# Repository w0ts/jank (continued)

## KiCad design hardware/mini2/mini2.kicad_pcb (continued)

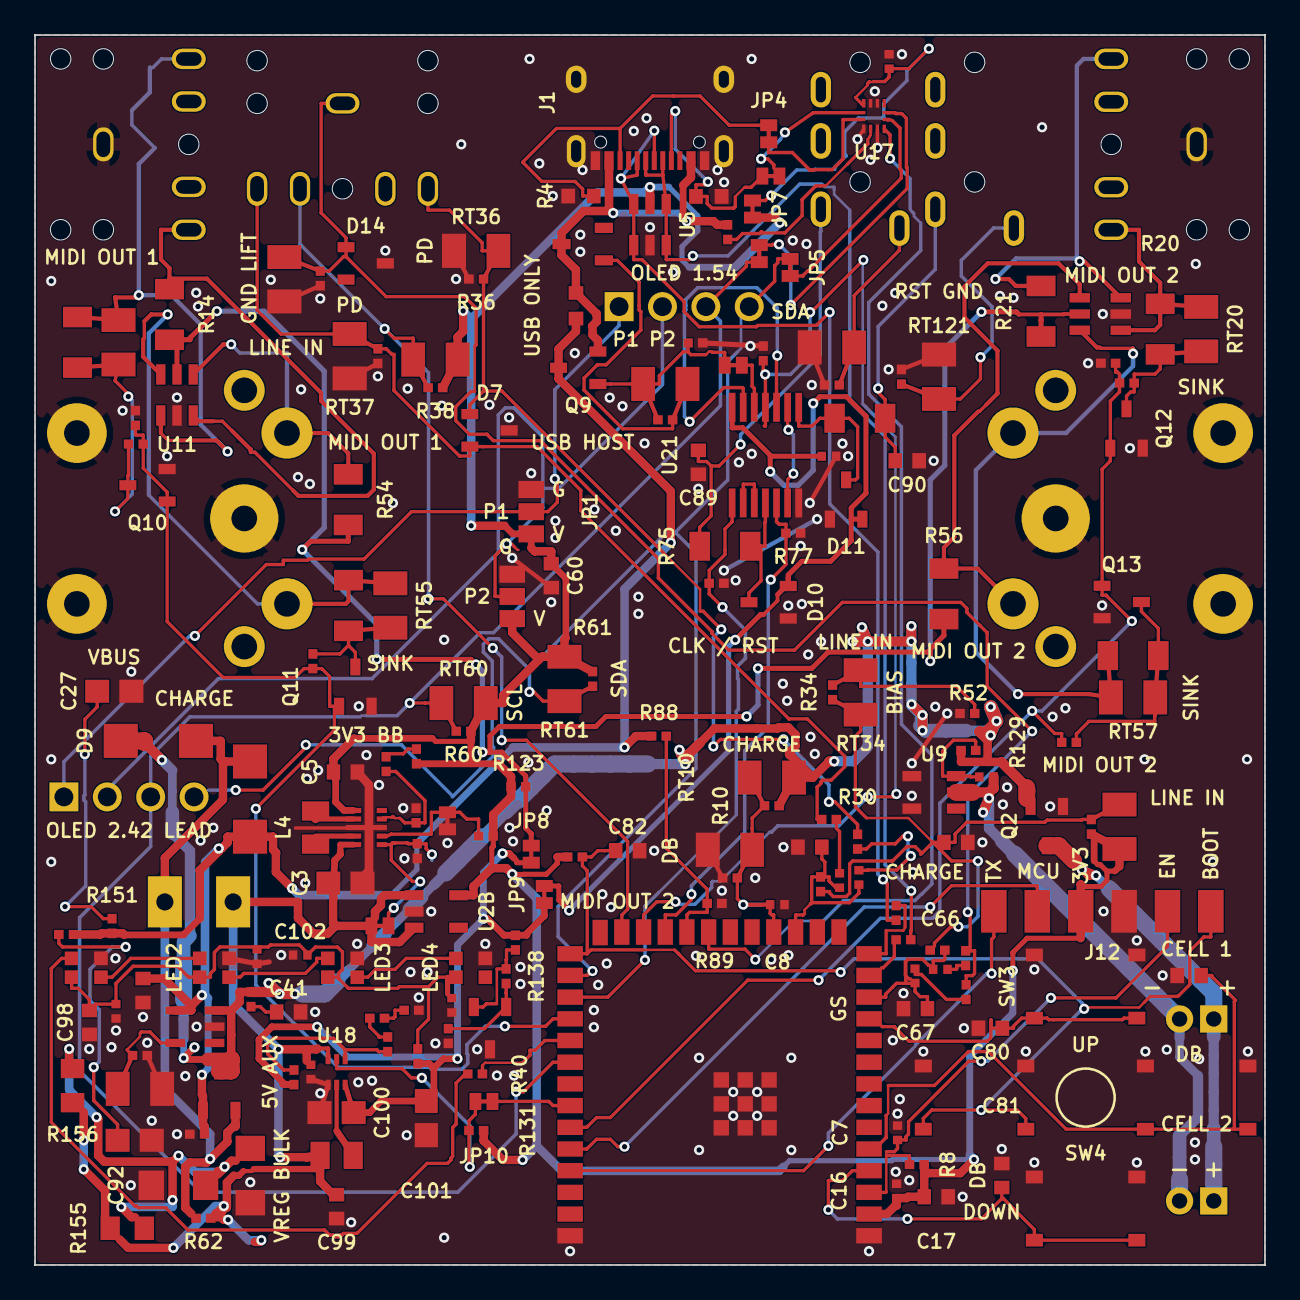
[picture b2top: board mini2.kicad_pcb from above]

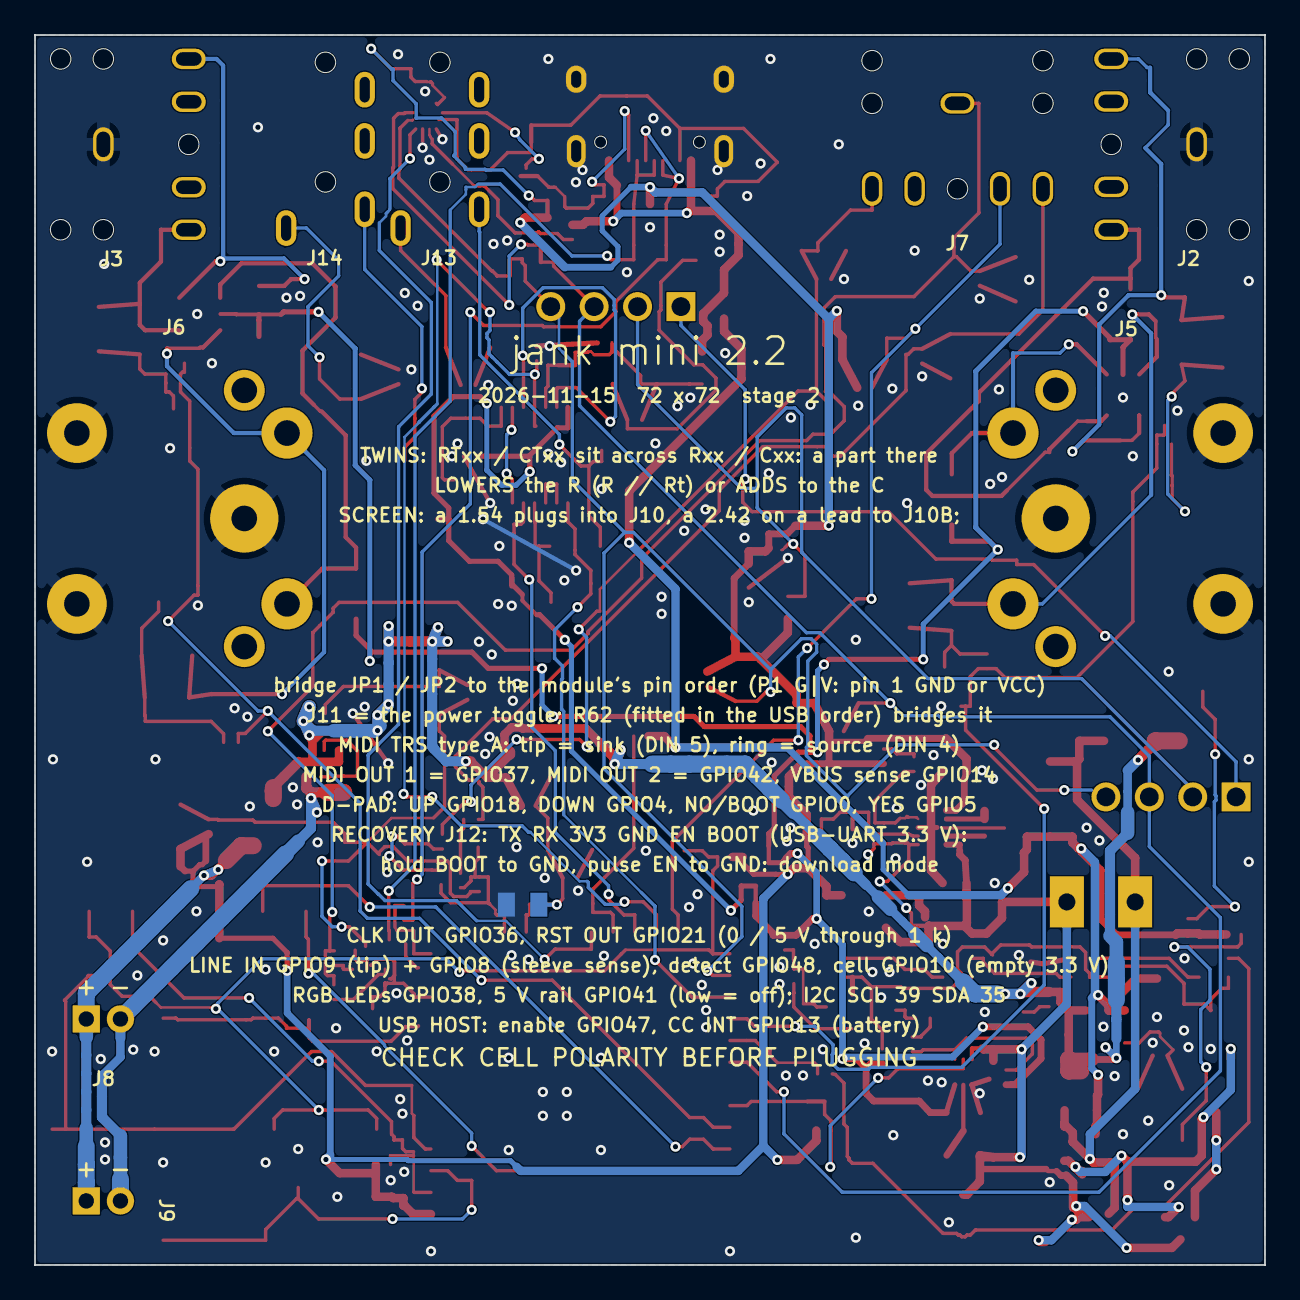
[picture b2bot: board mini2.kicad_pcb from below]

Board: 2 copper layers, 72.0 x 72.0 mm, 195 parts (10 on the bottom side), 105 nets.

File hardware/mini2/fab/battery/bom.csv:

"Comment","Designator","Footprint","LCSC Part #"
"22u","C3","C0805","C45783"
"22u","C5,C17","C0603","C59461"
"1u","C7,C30,C31,C65,C66","C0402","C52923"
"100n","C8,C16,C42,C95,C96,C97,C102,C103,C105","C0402","C1525"
"10u 25V","C27,C91,C100,C101","C0805","C15850"
"2.2n C0G","C32,C67,C89,C90","C0603","C2991172"
"10u","C33,C40,C41,C60,C98,C99","C0603","C19702"
"100u","C72,C92","C1206","C15008"
"10u","C104","C0402","C15525"
"SS34","D3,D9","SMA_L4.3-W2.6-LS5.2-RD","C8678"
"PESD15VL2BT","D7,D14","SOT-23_L2.9-W1.3-P1.90-LS2.4-BR","C38838"
"BAV99","D10,D11","SOT-23_L2.9-W1.3-P1.90-LS2.4-BR","C2500"
"BAT54C","D16","SOT-23-3_L2.9-W1.6-P1.90-LS2.8-BR","C37704"
"USB-C 16P","J1","USB-C-SMD_TYPE-C-16PIN-2MD-073","C2765186"
"0.47u","L4,L5","IND-SMD_L2.0-W1.6-1","C668312"
"WS2812C-2020-V6","LED1,LED2,LED3,LED4","LED-SMD_4P-L2.2-W2.0-P1.00_WS2815C-2020-4P","C55109522"
"AO3401A","Q1,Q2,Q9","SOT-23_L2.9-W1.3-P1.90-LS2.4-BR","C15127"
"AO3400A","Q10,Q11,Q12,Q13","SOT-23_L2.9-W1.3-P1.90-LS2.4-BR","C20917"
"10k","R8,R16","R0402","C25744"
"1M","R10,R11,R38,R134","R0402","C26083"
"220","R14,R15,R20,R21,R54,R55,R56,R57","R1206","C17957"
"22","R24,R25,R40","R0402","C25092"
"20k","R30,R31,R65,R66,R92,R138,R139,R142,R153,R154","R0402","C25765"
"12k","R32,R51,R67,R146","R0402","C25752"
"150k","R33,R89","R0402","C25755"
"100k","R34,R36,R37,R50,R71,R77,R88,R91,R124,R125,R131,R135,R140,R141","R0402","C25741"
"100","R39,R52,R120,R121","R0402","C25076"
"2.2k","R60,R61,R93","R0402","C25879"
"1k","R75,R81","R1206","C4410"
"1","R86,R151,R152","R0402","C25086"
"910k","R94","R0402","C25800"
"10","R98,R145","R0402","C25077"
"22k","R136","R0402","C25768"
"1","R155,R156","R0805","C25271"
"DOWN / UP / YES / NO / BOOT","SW1,SW3,SW4,SW5","SW-SMD_4P-L5.1-W5.1-P3.70-LS6.5-TL_H1.5","C318884"
"ESP32-S3-WROOM-1U-N8R2","U1","WIRELM-SMD_ESP32-S3-WROOM-1U","C3013944"
"TPS63802DLAR","U2","VSON-10_L3.0-W2.0-P0.50-TL","C2845237"
"SRV05-4","U5,U11,U12","SOT-23-6_L2.9-W1.6-P0.95-LS2.8-BL-1","C7420376"
"TP4054-42","U8","SOT-23-5_L3.0-W1.7-P0.95-LS2.8-BL","C32574"
"XB5353A","U9","SOT-23-5_L3.0-W1.7-P0.95-LS2.8-BR","C80628"
"TUSB320LIRWBR","U17","X2QFN-12_L1.6-W1.6-P0.40-TL","C2836598"
"TPS61023DRLR","U18","SOT-563_L1.6-W1.2-P0.50-LS1.6-BR","C919459"
"CJ431","U19","SOT-23-3_L2.9-W1.6-P1.90-LS2.8-BR","C3113"
"74AHCT04","U21","TSSOP-14_L5.0-W4.4-P0.65-LS6.4-BL","C8190"

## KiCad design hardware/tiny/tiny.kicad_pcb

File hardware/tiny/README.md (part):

# Jank tiny: a small board anyone orders assembled from JLCPCB

Part of the **[Jank device](../../README.md)** · the study behind it: [docs/dongle.md](../../docs/dongle.md) · the
bigger board: [hardware/pcb](../pcb/README.md)

One board, two uses. **With a computer on USB-C it is the Jank stick** (network adapter, USB-MIDI, the drive).
**Alone, plugged into a piece of gear's MIDI OUT or THRU, it runs from that output's few milliamps** and sends jank's
MIDI clock into the gear's MIDI IN. An ESP32-S3-MINI-1-N8 module, a USB-C on the top edge, a 3.5 mm TRS jack on each side
(left: MIDI OUT, right: POWER IN, both via TRS-to-DIN type A adaptors), one button, one LED, a 4.4 mF reservoir and a
60 nA buck. Everything is generated by the scripts here, from one parts table (`parts.py`).

> **Stage: design for review (2026-11-10).** Nothing is ordered, built or measured. Every figure marked *unverified*
> comes from a drawing, a datasheet or an estimate, not from a part in hand. Prices and stock are one snapshot
> (`fab/parts-snapshot.json`, read 2026-11-10 from JLCPCB's parts search), not a quote.

**Two variants, from the same schematic and scripts** (the user's ruling 2026-11-10: halve the area; cost both):

| | **tiny** (the board) | tiny-1s (for comparison) |
|---|---|---|
| Size | **27.0 x 36.0 mm** (972 mm²) | 42.0 x 44.0 mm (1848 mm²) |
| Sides | **two**: the cans, the jacks and small parts on the bottom (JLC *Standard* assembly) | one (JLC *Economic* assembly) |
| Board, assembly files | `tiny.kicad_pcb`, `fab/` | `tiny-1s.kicad_pcb`, `fab/1s/` |
| Renders, mockup | `render-top.png`, `render-bottom.png`, `mockup.stl` | `render-top-1s.png`, `render-bottom-1s.png`, `mockup-1s.stl` |
| Case | `case/` (made for this one) | none |

The cost of each, at 5 and 30 boards: **"Cost"** below (`fab/cost.md`).

## Files

| File | What |
|---|---|
| `parts.py` | **The parts table**: every part, its value, JLC footprint, LCSC code and the net on each pad; the GPIO map |
| `fetch_jlc.sh` | Fetches JLC's own footprints (EasyEDA, via easyeda2kicad 1.0.1) into `lib/jlc.pretty` (committed; run only to refresh) |
| `make_footprints.py` | `lib/tiny.pretty`: the JLC footprints with their silkscreen dropped, peg holes made unplated and courtyards redrawn; the cable pads |
| `make_schematic.py` | `tiny.kicad_sch` (every pin labelled, no wires), `tiny.kicad_pro`, `lib/tiny.kicad_sym`, `fab/intended-nets.json` |
| `route.py` | A small two-layer grid router (A*, vias, clearance masks per track width): no autorouter is installed here |
| `make_board.py` | `tiny.kicad_pcb` / `tiny-1s.kicad_pcb` (`VARIANT=2s|1s`): placement, routing (with rip-up and retry), ground pours, the antenna keep-out, stitching |
| `check_nets.py` | The schematic's netlist against `parts.py`, every board pad against it, the pin rules (no strapping pin, ADC1, RTC GPIOs) |
| `make_assembly.py` | `bom.csv`, `cpl.csv` for JLCPCB; checks every part's pads against JLC's own footprint at the CPL place |
| `jlc_parts.py` | `fab/parts-snapshot.json`: stock, price breaks, Basic / Extended, from JLCPCB's public parts search |
| `cost.py` | `fab/cost.md`: the estimate per variant at 5 and 30 boards |
| `make_mockup.py` | `mockup.stl`: the board and every part as a block, one closed solid (`../check_stl.py`) |
| `make_fab.sh` | **All of it in order**, both variants, then the cost and the case |
| `case/` | `tiny_case.scad`, `make_stl.sh`, `stl/` (base, lid, button cap), `assembly.png` |
| `tiny.kicad_dru` | The one DRC exception (below) |

```
sh hardware/tiny/make_fab.sh        # KiCad 10 (kicad-cli + its Python), python3, OpenSCAD; ~15 min (the router)
ROUTE=0 sh hardware/tiny/make_fab.sh   # keep the routed boards, redo the checks and outputs
```

**For JLCPCB:** `fab/tiny-gerbers.zip` (2 layers, 1.6 mm), `fab/bom.csv`, `fab/cpl.csv`.

## Schematic

```
 J3 POWER IN (gear's MIDI OUT/THRU)            USB-C J1
   ring (DIN 4) -- R1 47R -- D1 B5819W --+       VBUS -- D3 B5819W -- R5 4.7R --+
   tip  (DIN 5) -- R2 47R -- D2 B5819W --+-- VSYS (C1 + C2: 2 x 2200 uF, C3 10 uF)
   sleeve (DIN 2) = GND                    |      CC1, CC2: 5.1k to GND (R3, R4); D+/D- to GPIO20/19
                                           +-- U2 TPS62842 VIN; R7 51k = 3.3 V; L1 2.2 uH; C5 22 uF -> +3V3
                                           +-- U3 BL8506-40 (4.0 V detector) -- D4 A1 --+
                         PWR_HOLD (GPIO4) ---------------------------- D4 A2 --+-- BUCK_EN (C4 100n, R6 10M to GND)
                         VBUS ---------------------------------------- D5 --- +
                                           +-- R10 1M -- VBANK_ADC (GPIO1, C8 100n) -- R11 1M -- GND
 J2 MIDI OUT (gear's MIDI IN)                 VBUS -- R12 100k -- VBUS_SENSE (GPIO2) -- R13 100k -- GND
   ring (DIN 4) -- R14 33R -- +3V3
   tip  (DIN 5) -- R15 10R -- MIDI_TX (GPIO21)
   sleeve (DIN 2) = GND                        +3V3 -- R8 10k -- EN, C7 1u;  GPIO0 -- SW1 -- GND;  GPIO38 -- R9 5.1k -- LED1 -- GND
```

### Power from a MIDI OUT

- **Both data pins feed the reservoir:** the ring (DIN pin 4, the sender's source through its 220 ohm) and the tip (DIN
  pin 5, high between bytes), each through **47 ohm** and a **B5819W** Schottky. Nothing flows back out: each diode
  blocks when its pin is below VSYS (the tip during a 0 bit, any pin when USB holds VSYS up), leaving only the diode's
  leakage (microamps, *unverified* at these voltages).
- **The 47 ohm current limit, the trade-off:** it lowers the current from a normal 5 V / 220 ohm output only a little
  at the operating point (bank at 4.0 V, Schottky 0.25 V: (5 - 0.25 - 4.0) / 267 = **2.8 mA a pin instead of 3.4 mA**,
  -18 %; the running equilibrium with ~2.3 mA drawn moves from ~4.50 V to ~4.46 V), but it guards weak drivers when the
  bank is empty: into a flat bank a 5 V / 220 ohm output gives 17.6 mA instead of 21 mA, a **3.3 V / 33 ohm output
  (CA-033) 38 mA instead of 92 mA**. Such 3.3 V gear cannot run the dongle anyway (the bank never reaches the start
  threshold), but it is not stressed either. 47 ohm is a JLC Basic part.
- **USB joins the same rail** through D3 (B5819W) and **R5 4.7 ohm**: USB wins when present (4.7 V against the bank's
  ~4.4 V). R5 limits the inrush into 4.4 mF to ~1 A (time constant ~21 ms) instead of an unlimited surge; in stick
  mode it drops ~0.47 V at 100 mA (47 mW). *Unverified:* the 0805's pulse rating for ~49 mJ per plug-in, and that every
  host tolerates the 1 A peak (USB 2.0 allows 10 uF at attach). A 1206 (Extended) is the safer choice if it is a
  concern.

### The reservoir (C1, C2: 2 x 2200 uF 6.3 V aluminium, 10 x 10.5 mm, **4.4 mF**)

- **The start:** the module may only start once the bank holds a whole boot: the detector releases the buck at
  **~4.16 V** (BL8506-40: 4.00 V falling, 0.16 V hysteresis typical, 4.0..4.32 V rising), and the module runs down to
  ~3.2 V at the bank (the buck in 100 % mode; the S3 needs 3.0 V). **~1.0 V x 4.4 mF = 4.4 mC: about 150 ms of boot at
  30 mA** (the boot's current and length are *unmeasured*: the study's "a few mF for a slow start").
- **The listening windows:** 0.6..0.8 mC each (the study's estimate) sag the bank only **0.15..0.18 V**.
- **Charging from a 5 V output:** both pins together give ~5..7 mA into an empty bank: **~3 s** to the start threshold.
- **Why these parts:** no supercap is placeable at JLC; MLCCs lose most of their capacitance at 4 V bias (dozens
  needed); tantalum is ~10x the price. Two 10 x 10 mm cans store the most per board area of the SMD aluminium parts
  JLC stocks (1000 uF 8 x 10: 88 mm²/mF of footprint; 2200 uF 10 x 10: 65 mm²/mF).
- **Leakage** (*unverified*, the one figure that matters most here): the datasheet's limit, 0.01 CV, is ~139 uA a can
  at rated voltage after 2 minutes; aluminium caps at 70 % of rating after hours typically leak a few percent of that.
  **Measure it**: it adds directly to the 3 mA budget.
- 6.3 V rating: the rail never exceeds VBUS (5.25 V, 5.5 V from a careless charger) minus a Schottky.

### 3.3 V: the TPS62842 buck (chosen) against an LDO

| | TPS62842DGRR (C2873354) + 2.2 uH | RT9080-33 LDO (C841192) | XC6206P332 LDO (C5446, Basic) |
|---|---|---|---|
| Quiescent current | **60 nA** (120 nA in 100 % mode) | 2 uA | 1 uA |
| Input current for 2.5 mA out at 4.4 V (85 % efficient, *the efficiency at this load unverified*) | **~2.2 mA** | 2.5 mA | 2.5 mA |
| Peak current (Wi-Fi TX in stick mode, ~350 mA) | 750 mA | 600 mA | **200 mA: too weak** |
| Price (snapshot) | $0.40 + $0.11 inductor, 2 Extended lines | $0.12, 1 Extended line | $0.13 Basic |

The buck saves ~0.3 mA of the ~2.5 mA the study budgets (12 %; more as the bank rises) for ~$0.40 a board and one
more Extended line: on a 5 mA source that is the margin. R7 = **51 k** sets 3.3 V (TI table 1: 50.21..54.39 k; 51 k is
a Basic part, 52.3 k is not). MODE low: power-save (PFM) mode.

### Start-up and holding the buck on (BUCK_EN)

BUCK_EN = the detector **or** VBUS **or** PWR_HOLD (GPIO4), through D4 / D5 (BAV70, nanoamp leakage). C4 (100 nF) and
R6 (10 M) keep it high **~1 s after** the detector drops (the buck's EN pull-down is off once it runs, TI datasheet
8.3): time for the firmware to raise PWR_HOLD. **The firmware must set PWR_HOLD high early (a bootloader hook if the
boot is slow) and keep it held in light and deep sleep** (an RTC GPIO: `rtc_gpio_hold_en`); releasing it below 4.0 V
switches everything off until the bank is back above ~4.16 V. A brown-out during the boot cannot loop: the timer ends,
the bank recharges, it starts again. With USB, VBUS holds BUCK_EN.

### Static draw, everything off (the bank charging, *datasheet typicals*)

Detector 0.5 uA, the VSYS divider 2.4 uA at 4.8 V, the buck's shutdown 25 nA, R6 0.4 uA while BUCK_EN is high, the
diodes' leakage: **~3 uA plus the cans' leakage**.

## Pin map (for the firmware's board.h)

| Function | GPIO | Module pin | Notes |
|---|---|---|---|
| **MIDI_TX** | **21** | 25 | UART TX (any UART by the GPIO matrix), idle high; through R15 10 ohm to the MIDI OUT tip. An RTC GPIO: the ULP can send the ticks. Not strapping |
| **LED** | **38** | 34 | active high, R9 5.1 k: ~0.27 mA lit (red, 1.9 V) |
| **BOOT / user button** | **0** | 4 | to GND; held at reset = download mode. Internal pull-up |
| **VBANK_ADC** | **1** | 5 | ADC1_CH0: VSYS / 2 (1 M / 1 M, 100 nF); 11 dB attenuation reads to ~3.1 V = 6.2 V at the bank |
| **VBUS_SENSE** | **2** | 6 | ADC1_CH1 or digital: VBUS / 2 (100 k / 100 k) = 2.5 V when USB is plugged |
| **PWR_HOLD** | **4** | 8 | high keeps the buck on; hold it through sleep (RTC GPIO) |
| USB D- / D+ | 19 / 20 | 23 / 24 | the native USB (stick mode) |
| EN | | 45 | RC reset (R8 10 k, C7 1 uF); no reset button |
| MIDI OUT ring | | | +3V3 through R14 33 ohm (0805) |

Not used, left open: everything else, including the strapping pins GPIO3, 45, 46 and the console UART (GPIO43 / 44).

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
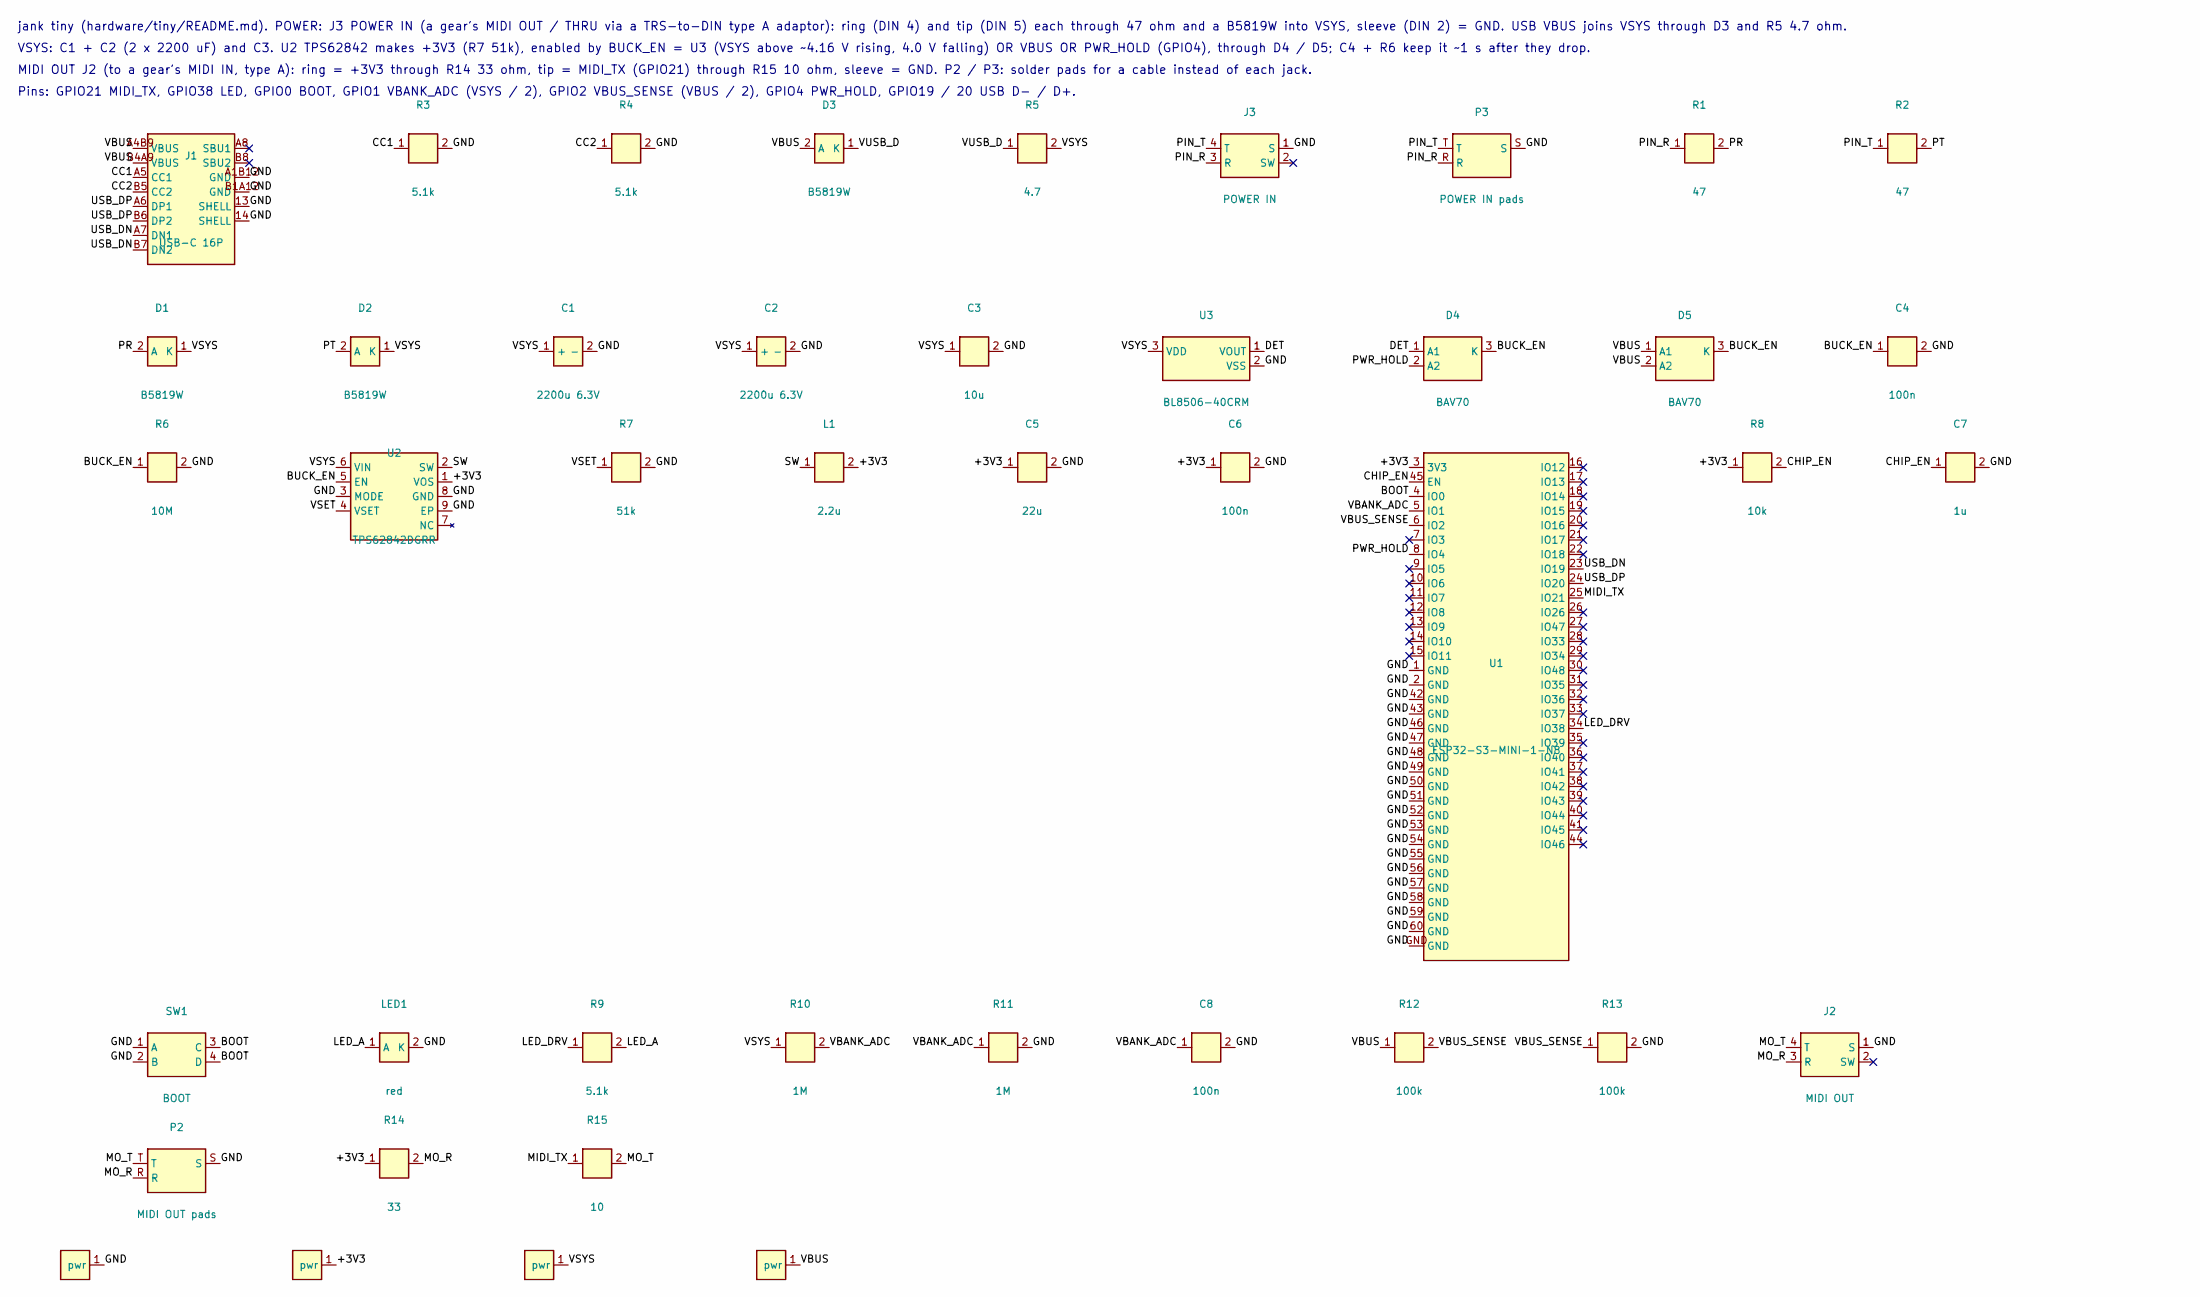
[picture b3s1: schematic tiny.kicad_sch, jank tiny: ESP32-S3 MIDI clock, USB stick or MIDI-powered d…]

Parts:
C1, C2: 2200u 6.3V; CAP-SMD_BD10.0-L10.3-W10.3-LS11.0-FD; LCSC C22383517
C3: 10u; C0805; LCSC C15850
C4, C6, C8: 100n; C0603; LCSC C14663
C5: 22u; C0805; LCSC C45783
C7: 1u; C0603; LCSC C15849
D1, D2, D3: B5819W; SOD-123_L2.7-W1.6-LS3.7-RD-1; LCSC C8598
D4, D5: BAV70; SOT-23-3_L3.0-W1.7-P0.95-LS2.9-BR; LCSC C68978
J1: USB-C 16P; USB-C-SMD_TYPE-C-16PIN-2MD-073; LCSC C2765186
J2: MIDI OUT; AUDIO-SMD_XKB_PJ-320D-B; LCSC C2884940
J3: POWER IN; AUDIO-SMD_XKB_PJ-320D-B; LCSC C2884940
L1: 2.2u; L0806; LCSC C79317
LED1: red; LED-SMD_L1.6-W0.8-R-RD; LCSC C2286
P2: MIDI OUT pads; TRS_PADS_3x1.0mm
P3: POWER IN pads; TRS_PADS_3x1.0mm
R1, R2: 47; R0603; LCSC C23182
R3, R4, R9: 5.1k; R0603; LCSC C23186
R5: 4.7; R0805; LCSC C17675
R6: 10M; R0603; LCSC C7250
R7: 51k; R0603; LCSC C23196
R8: 10k; R0603; LCSC C25804
R10, R11: 1M; R0603; LCSC C22935
R12, R13: 100k; R0603; LCSC C25803
R14: 33; R0805; LCSC C17634
R15: 10; R0603; LCSC C22859
SW1: BOOT; SW-SMD_4P-L5.1-W5.1-P3.70-LS6.5-TL_H1.5; LCSC C318884
U1: ESP32-S3-MINI-1-N8; BULETM-SMD_ESP32-S3-MINI-1-N8; LCSC C2913206
U2: TPS62842DGRR; HVSSOP-8_L3.0-W3.0-P0.65-LS4.9-BL-EP; LCSC C2873354
U3: BL8506-40CRM; SOT-23-3_L2.9-W1.6-P1.90-LS2.8-BR; LCSC C2909397

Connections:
+3V3: C5.1, C6.1, L1.2, R8.1, R14.1, U1.3 (3V3), U2.1 (VOS)
BOOT: SW1.3 (C), SW1.4 (D), U1.4 (IO0)
BUCK_EN: C4.1, D4.3 (K), D5.3 (K), R6.1, U2.5 (EN)
CC1: J1.A5 (CC1), R3.1
CC2: J1.B5 (CC2), R4.1
CHIP_EN: C7.1, R8.2, U1.45 (EN)
DET: D4.1 (A1), U3.1 (VOUT)
GND: C1.2 (-), C2.2 (-), C3.2, C4.2, C5.2, C6.2, C7.2, C8.2, J1.13 (SHELL), J1.14 (SHELL), J1.A1B12 (GND), J1.B1A12 (GND), J2.1 (S), J3.1 (S), LED1.2 (K), P2.S, P3.S, R3.2, R4.2, R6.2, R7.2, R11.2, R13.2, SW1.1 (A), SW1.2 (B), U1.1 (GND), U1.2 (GND), U1.42 (GND), U1.43 (GND), U1.46 (GND), U1.47 (GND), U1.48 (GND), U1.49 (GND), U1.50 (GND), U1.51 (GND), U1.52 (GND), U1.53 (GND), U1.54 (GND), U1.55 (GND), U1.56 (GND), U1.57 (GND), U1.58 (GND), U1.59 (GND), U1.60 (GND), U1.GND, U2.3 (MODE), U2.8 (GND), U2.9 (EP), U3.2 (VSS)
LED_A: LED1.1 (A), R9.2
LED_DRV: R9.1, U1.34 (IO38)
MIDI_TX: R15.1, U1.25 (IO21)
MO_R: J2.3 (R), P2.R, R14.2
MO_T: J2.4 (T), P2.T, R15.2
PIN_R: J3.3 (R), P3.R, R1.1
PIN_T: J3.4 (T), P3.T, R2.1
PR: D1.2 (A), R1.2
PT: D2.2 (A), R2.2
PWR_HOLD: D4.2 (A2), U1.8 (IO4)
SW: L1.1, U2.2 (SW)
USB_DN: J1.A7 (DN1), J1.B7 (DN2), U1.23 (IO19)
USB_DP: J1.A6 (DP1), J1.B6 (DP2), U1.24 (IO20)
VBANK_ADC: C8.1, R10.2, R11.1, U1.5 (IO1)
VBUS: D3.2 (A), D5.1 (A1), D5.2 (A2), J1.A4B9 (VBUS), J1.B4A9 (VBUS), R12.1
VBUS_SENSE: R12.2, R13.1, U1.6 (IO2)
VSET: R7.1, U2.4 (VSET)
VSYS: C1.1 (+), C2.1 (+), C3.1, D1.1 (K), D2.1 (K), R5.2, R10.1, U2.6 (VIN), U3.3 (VDD)
VUSB_D: D3.1 (K), R5.1

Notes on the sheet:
jank tiny (hardware/tiny/README.md). POWER: J3 POWER IN (a gear's MIDI OUT / THRU via a TRS-to-DIN type A adaptor): ring (DIN 4) and tip (DIN 5) each through 47 ohm and a B5819W into VSYS, sleeve (DIN 2) = GND. USB VBUS joins VSYS through D3 and R5 4.7 ohm.
VSYS: C1 + C2 (2 x 2200 uF) and C3. U2 TPS62842 makes +3V3 (R7 51k), enabled by BUCK_EN = U3 (VSYS above ~4.16 V rising, 4.0 V falling) OR VBUS OR PWR_HOLD (GPIO4), through D4 / D5; C4 + R6 keep it ~1 s after they drop.
MIDI OUT J2 (to a gear's MIDI IN, type A): ring = +3V3 through R14 33 ohm, tip = MIDI_TX (GPIO21) through R15 10 ohm, sleeve = GND. P2 / P3: solder pads for a cable instead of each jack.
Pins: GPIO21 MIDI_TX, GPIO38 LED, GPIO0 BOOT, GPIO1 VBANK_ADC (VSYS / 2), GPIO2 VBUS_SENSE (VBUS / 2), GPIO4 PWR_HOLD, GPIO19 / 20 USB D- / D+.

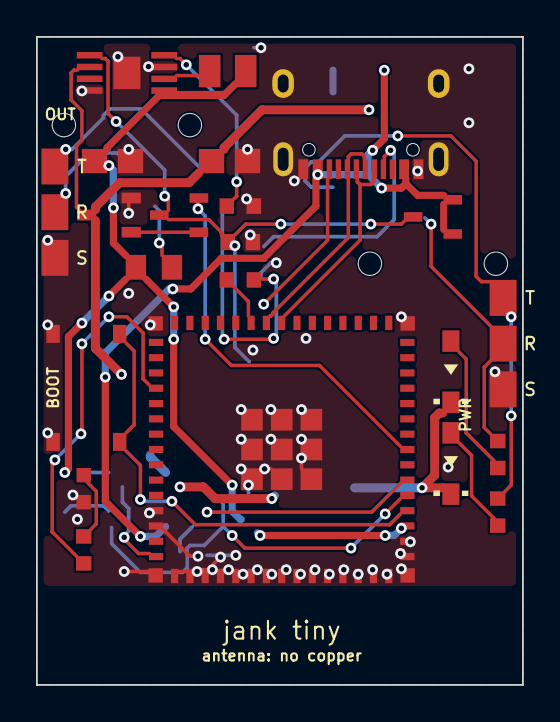
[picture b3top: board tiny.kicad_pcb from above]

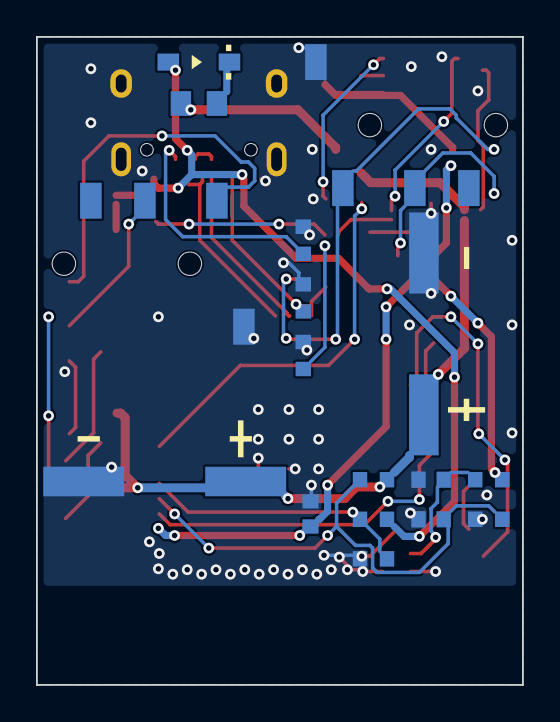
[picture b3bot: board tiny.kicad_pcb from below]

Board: 2 copper layers, 27.0 x 36.0 mm, 39 parts (17 on the bottom side), 27 nets.

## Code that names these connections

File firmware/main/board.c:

/* SPDX-License-Identifier: GPL-3.0-only */
/* The boards' pin tables and, in the auto build, which board this is (board.h). The values are the ones board.h held
 * per build until 2026-11-22; their sources stay in the comments. */
#include "board.h"
#include "esp_attr.h"
#include "esp_flash.h"
#include "esp_log.h"

static const char *TAG = "board";

#if CONFIG_JANK_BOARD_XIAO || CONFIG_JANK_BOARD_AUTO
/* Seeed XIAO ESP32S3. D6 = GPIO43 for MIDI data, the board's 3V3 pad the source; the module has 499 ohm in series on D6
 * (v1.2 schematic, R6): MIDI current about 2.3 mA (docs/boards.md). The button is BOOT, the LED the single yellow one
 * (GPIO21, active low). No CC chip, no 5 V of its own, no line in: USB host mode through an OTG adapter with self-powered
 * gear. Bench outputs (midi.c): D1 = GPIO2 changes level on every MIDI clock, D0 = GPIO1 goes high with each start
 * (docs/midi.md). The UI bench (JANK_UI_BENCH): a 128 x 64 I2C OLED on D4 = GPIO5 SDA / D5 = GPIO6 SCL, UP D3 = GPIO4,
 * DOWN D8 = GPIO7, YES D9 = GPIO8, NO D10 = GPIO9 or BOOT. The LINE IN bench (JANK_LINEIN_BENCH): pad D3 = GPIO4
 * (ADC1_CH3) through a bias network (docs/linein.md), no cell, no plug detect. */
static DRAM_ATTR const struct board XIAO = {
    .name = "xiao", .model = "XIAO",
    .button_gpio = 0, .button_active_low = 1,
    .led_rgb_gpio = -1, .led_mono_gpio = 21, .led_count = 1,
    .midi_tx_gpio = 43, .midi_source_gpio = -1, .midi_tx_more = {-1, -1}, .midi_tx_invert = 0, .midi_tx_drive = -1,
    .bench_clk_gpio = 2, .bench_rst_gpio = 1,
    .clk_gpio = -1, .rst_gpio = -1, .v5_en_gpio = -1,
#if CONFIG_JANK_UI_BENCH
    .i2c_sda_gpio = 5, .i2c_scl_gpio = 6,
    .btn_up_gpio = 4, .btn_down_gpio = 7, .btn_yes_gpio = 8, .btn_no2_gpio = 9, .oled = 1,
#else
    .i2c_sda_gpio = -1, .i2c_scl_gpio = -1,
    .btn_up_gpio = -1, .btn_down_gpio = -1, .btn_yes_gpio = -1, .btn_no2_gpio = -1, .oled = 0,
#endif
    .lcd = 0, .lcd_mosi_gpio = -1, .lcd_sclk_gpio = -1, .lcd_cs_gpio = -1, .lcd_dc_gpio = -1, .lcd_rst_gpio = -1, .lcd_bl_gpio = -1,
    .cc_scl_gpio = -1, .cc_sda_gpio = -1, .cc_int_gpio = -1,
    .host_en_gpio = -1, .vbus_sense_gpio = -1, .line_detect_gpio = -1, .pump_gpio = -1,
    .usbport_tusb320 = 0, .usbport_mini3 = 0,
    .bridge_slots_psram = 1,              /* (2026-11-22: with both boards' drivers in one image the 30 KB no longer fit in
                                             internal RAM: ui_start failed with ESP_ERR_NO_MEM, measured with `diag`) */
    .host_audio = 0,                      /* host mode: no audio client, no beat tracker: the Digitone and the Launchpad together need the RAM
                                             (the second one's claim failed with ESP_ERR_NO_MEM, 2026-11-24); the tracker did not run there anyway */
#if CONFIG_JANK_LINEIN_BENCH
    .has_linein = 1, .linein_gpio = 4,
#else
    .has_linein = 0, .linein_gpio = -1,
#endif
    .linesense_gpio = -1, .cell_gpio = -1, .cell_div = 1, .cell_empty_mv = 0,
};
#endif

#if CONFIG_JANK_BOARD_LCD2 || CONFIG_JANK_BOARD_AUTO
/* Waveshare ESP32-S3-LCD-2 (sku 30306, ESP32-S3R8, 16 MB flash) on the jank mini 3, pins from the LCD-2's schematic and
 * hardware/jank-mini-3/parts.py (docs/lcd2.md has the sources and what is not verified). The screen: 240 x 320 ST7789 on
 * SPI, landscape (lcd.c); LCD_RST is GPIO0 through R16 "NC/0R" (the panel is reset by command); backlight GPIO1 high.
 * NO is BOOT and GPIO21; MIDI OUT 1 GPIO13 (J16.8) and OUT 2 GPIO9 (J16.12) from one UART TX, inverted (AO3400A sinks: the
 * line idles low). HOST_EN 17 only through usbport_mini3.c; VBUS_SENSE 10 (10 k / 15 k: 3.0 V at 5 V); LIN_DET 18 (high =
 * a plug); LINE IN node A GPIO7 (ADC1_CH6), node B GPIO8 (not sampled yet); the cell on BAT_ADC GPIO5 (R19 200 k / R20
 * 100 k: a third); V5_EN 4, CLK 15, RST 2 (power.c drives them at boot). Bridge slots in PSRAM: internal DRAM is full. */
static DRAM_ATTR const struct board LCD2 = {
    .name = "lcd2", .model = "LCD2",
    .button_gpio = 0, .button_active_low = 1,
    .led_rgb_gpio = -1, .led_mono_gpio = -1, .led_count = 0,
    .midi_tx_gpio = 13, .midi_source_gpio = -1, .midi_tx_more = {9, -1}, .midi_tx_invert = 1, .midi_tx_drive = -1,
    .bench_clk_gpio = -1, .bench_rst_gpio = -1,
    .clk_gpio = 15, .rst_gpio = 2, .v5_en_gpio = 4,
    .i2c_sda_gpio = -1, .i2c_scl_gpio = -1,
    .btn_up_gpio = 11, .btn_down_gpio = 6, .btn_yes_gpio = 16, .btn_no2_gpio = 21, .oled = 0,
    .lcd = 1, .lcd_mosi_gpio = 38, .lcd_sclk_gpio = 39, .lcd_cs_gpio = 45, .lcd_dc_gpio = 42, .lcd_rst_gpio = -1, .lcd_bl_gpio = 1,
    .cc_scl_gpio = -1, .cc_sda_gpio = -1, .cc_int_gpio = -1,
    .host_en_gpio = 17, .vbus_sense_gpio = 10, .line_detect_gpio = 18, .pump_gpio = -1,
    .usbport_tusb320 = 0, .usbport_mini3 = 1, .bridge_slots_psram = 1, .host_audio = 1,
    .has_linein = 1, .linein_gpio = 7, .linesense_gpio = 8,
    .cell_gpio = 5, .cell_div = 3, .cell_empty_mv = 3300,
};
#endif

#if CONFIG_JANK_BOARD_MINI22
/* jank mini 2.2 (ESP32-S3-WROOM-1U-N8R2), from hardware/mini2/parts.py and README.md on hw/mini2.2 (2026-11-15): NO = BOOT
 * (SW1), two WS2812B-2020 on GPIO35, the D-pad 10 / 37 / 36 to GND, the screen J10 on I2C SCL 11 / SDA 12 (R60 / R61 10 k),
 * MIDI OUT 1 UART GPIO21 (68 ohm sinks, drive 3), U17 TUSB320LI at 0x47 on the same I2C with INT_N 39, HOST_EN 42, VBUS
 * sense 38 (R88 22 k / R89 33 k), LINE IN plug switch 16 (low = no plug), LINE IN GPIO9 (ADC1_CH8), the cell GPIO4 (ADC1_CH3,
 * R10 / R11 100 k / 100 k), empty at ~3.3 V (the TPS63802). */
static DRAM_ATTR const struct board MINI22 = {
    .name = "mini22", .model = "MINI 2.2",
    .button_gpio = 0, .button_active_low = 1,
    .led_rgb_gpio = 35, .led_mono_gpio = -1, .led_count = 2,
    .midi_tx_gpio = 21, .midi_source_gpio = -1, .midi_tx_more = {-1, -1}, .midi_tx_invert = 0, .midi_tx_drive = 3,
    .bench_clk_gpio = -1, .bench_rst_gpio = -1,
    .clk_gpio = -1, .rst_gpio = -1, .v5_en_gpio = -1,
    .i2c_sda_gpio = 12, .i2c_scl_gpio = 11,
    .btn_up_gpio = 10, .btn_down_gpio = 37, .btn_yes_gpio = 36, .btn_no2_gpio = -1, .oled = 1,
    .lcd = 0, .lcd_mosi_gpio = -1, .lcd_sclk_gpio = -1, .lcd_cs_gpio = -1, .lcd_dc_gpio = -1, .lcd_rst_gpio = -1, .lcd_bl_gpio = -1,
    .cc_scl_gpio = 11, .cc_sda_gpio = 12, .cc_int_gpio = 39,
    .host_en_gpio = 42, .vbus_sense_gpio = 38, .line_detect_gpio = 16, .pump_gpio = -1,
    .usbport_tusb320 = 1, .usbport_mini3 = 0, .bridge_slots_psram = 0, .host_audio = 1,
    .has_linein = 1, .linein_gpio = 9, .linesense_gpio = -1,
    .cell_gpio = 4, .cell_div = 2, .cell_empty_mv = 3300,
};
#endif

#if CONFIG_JANK_BOARD_XIAO || CONFIG_JANK_BOARD_AUTO
DRAM_ATTR const struct board *g_board = &XIAO;
#elif CONFIG_JANK_BOARD_LCD2
DRAM_ATTR const struct board *g_board = &LCD2;
#elif CONFIG_JANK_BOARD_MINI22
DRAM_ATTR const struct board *g_board = &MINI22;
#else
#error "no board chosen"
#endif

static const char *s_how = "built for it";

const char *board_how(void)
{
    return s_how;
}

#if CONFIG_JANK_BOARD_AUTO
/* The two boards differ in their flash chip: the LCD-2 has a 16 MB W25Q128 (docs/lcd2.md, its schematic U5), the XIAO 8 MB
 * (one measured 2026-11-22: GigaDevice c8 4017, 8 MB). The chip says its own size: no pin is touched. (A first version
 * probed the LCD-2's motion sensor on GPIO47 / 48; on the XIAO that hung the start, measured 2026-11-22.) A XIAO "Plus"
 * (16 MB) would be taken for the LCD-2: it is not a supported board. */
void board_init(void)
{
    uint32_t flash = 0;
    if (esp_flash_get_physical_size(NULL, &flash) != ESP_OK)
        flash = 0;
    if (flash >= 16u * 1024u * 1024u) {
        g_board = &LCD2;
        s_how = "flash 16 MB";
    } else {
        g_board = &XIAO;
        s_how = flash ? "flash 8 MB" : "default";
    }
    ESP_LOGI(TAG, "%s (%s; flash %lu MB)", g_board->name, s_how, (unsigned long)(flash >> 20));
}
#else
void board_init(void)
{
    ESP_LOGI(TAG, "%s (built for it)", g_board->name);
}
#endif

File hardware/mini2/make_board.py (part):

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CX, CY = 18.8 + S, GE - max(13.5, 12.1 + (H0 - 52.5) * 0.4)   # (13.5 or more: the crystal clear of J4)    # the chip's centre (turned 180: LNA_IN at the right side's bottom)
# 2026-11-15 (the user's): U1 is an ESP32-S3-WROOM-1U-N8R2 module. MODULE: the bare chip's drawn copper (the RF line,
# the fan-out lanes, the crystal and VDD3P3 hops, the exposed pad's vias and blocks) is skipped; the module sits at
# MOD_XY turned 180 (its u.FL toward the bottom edge, its top pin row (15 .. 26: LINE_IN, I2C, BTN_UP, MIDI_TX) up
# toward the LINE IN block and the header, USB (13 / 14) at its upper right)
MODULE = True
MOD_XY = (38.6, 61.5)
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    # (stage 2, CLOCK / RESET: the drivers in two rows of three SOT-23 right of the cell's protection (2N7002, AO3401A,
    #  BAV99), the outputs' 2 k pairs on the right edge, the gate pull-downs between the rows and Q2, the nodes'
    #  pull-downs over the rows; the charge pump (R83, C84, D12, D13, C85, R84) between the chip's right side and the
    #  cross, by GPIO5's pin; the gate pull-ups with their twins beside them; README "CLOCK / RESET")
    "Q3": (50.4, 39.6, 0), "Q4": (54.2, 39.6, 0), "D10": (58.1, 39.6, 0),
    "Q5": (50.4, 43.15, 0), "Q6": (54.2, 43.15, 0), "D11": (58.1, 43.15, 0),
    "R75": (62.9, 37.5, 0), "R76": (62.9, 40.1, 0), "R81": (62.9, 42.7, 0), "R82": (62.9, 45.3, 0),
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    "RT73": (57.0, 34.6, 0), "R73": (57.0, 36.7, 0), "RT79": (62.9, 48.5, 0), "R79": (62.9, 50.6, 0),
    # (review pass 1: the nodes' 4.7 nF, C89 over D10, C90 under R80 (RST_N's pull-down): no switch-on blip)
    "C89": (58.1, 36.9, 0), "C90": (46.0, 36.8, 0),
    # (the pump at the board's lower left, by GPIO35's pin and VREG, far from LINE IN; raw: + DX2, + BAND - 6)
    # (review pass 1: U13, the pump's buffer, and its 100 nF where U10 was; R83 / C84 between it and the diodes, which
    #  moved 0.6 mm right for C3 at the LDO)
    # (2026-11-15: the pump is gone; in its place, absolute: the 5 V aux rail's boost U18, L5 and its caps, the rest of the
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    # mini 2.2, the power and the cell (README "mini 2.2 simplified"): the lower left, where the buck and C1 were, under
    # the DIN pads' iron room (y 39 on): the two PH2.0 sockets (bottom side, DNP) on one row near the ground edge, the
    # protector (U9) and the charger (U8) above them, the power path (D3, Q1) and the 3.3 V LDO (U2) towards the chip;
    # the cell's divider (R10 / R11 / C8) at its fan-out lane (GPIO4 since stage 2), above the chip's right side
    # (stage 1d: the cells stand on edge under the board in y 39..58, beside the DIN bodies: the two sockets moved out of
    #  that band to the middle, y 33, between the DIN bodies; their bodies hang under the board there)
    "J8": (62.0, 57.6, 0, "B"), "J9": (62.0, 68.25, 0, "B"),   # (buffer try, the user's: bottom right above SW3, vertical B2B   # (buffer try, the user's: bottom right, above SW3, by the cells' lead end)
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    "R86": (16.2, 44.5, 90),                        # (review pass 1: C41's 1 ohm, beside it)
    "D9": (13.0, 41.6, 0),                 # (review pass 2: an SS34 (SMA) beside U15, BAT_P -> VSYS)
    # the 3.3 V LDO (review pass 2: a TLV757P, WSON-6, both orders): C3 right of IN (pin 6), C5 / C6 left of OUT
    # (pin 1); D15 (OUT -> IN) under it; C72 / C92 (VREG bulk behind R155, both orders since sign-off stage 2) at the left edge
    "U2": (10.0, 54.0, 0),
    "C3": (10.0, 50.9, 0), "C5": (7.4, 53.6, 90), "C6": (5.9, 53.6, 90), "C92": (2.6, 53.75, 90),   # (2026-11-15: C3 above U2)
    # (stage 2: the cell's divider and its twins in the middle, between the header and the sockets)
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    # mini 2, LINE IN (README "LINE IN"): J7 on the top edge (its bushing up) between J2 and the USB-C, tip / ring pads on its
    # right; D7 by them; the summer's inputs (R30 / C30 tip, R31 / C31 ring) to U6 (turned: IN- and IN+ on top, OUT and V+
    # below), R32 // C32 on its left from IN- to OUT, the bias (R33 / R34 / C33) on its right; the LDO (U7, C34 in, C35 out)
    # in the top strip by the USB-C (VBUS); R35 / C36 at the chip's GPIO9 (pin 14), the right side's top corner
    # stage 2: J7 a PJ-307C (tip pin 5 on the right, ring pin 2 on the left, the ring's switch pin 3: LIN_DET); each TVS
    # by its pin (D7 tip, upright right of J7; D8 ring, under J2 / J7's legs); the front end in a block of its own in the
    # board's empty middle-left (x 21.5 .. 29.5, y 16.5 .. 31: under the screen module, all low parts), 12 mm from the
    # chip, away from the RF corner, each resistor with its twin pads; its LDO (U7) in the block (VSYS in, AVDD short)
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    "D14": (25.0, 12.9, 0),        # (review pass 2, L7: the sleeve's TVS, by R39; + the x shift: 28.0)
    # (stage 2, the hand-solder twins: the inputs, pull-downs and detect with their twins in a column left of the USB
    #  pair, AVDD's LDO beside them; the summer, its gain and bias with their twins right of the pair, by the chip's
    #  LINE_IN pin: only LIN_SUM and AVDD cross the pair)
    "R30": (19.95, 19.5, 0), "RT30": (19.95, 21.15, 0), "R31": (19.95, 23.5, 0), "RT31": (19.95, 25.15, 0),
    "R36": (19.95, 27.5, 0), "RT36": (19.95, 29.15, 0), "R37": (19.95, 31.5, 0), "RT37": (19.95, 33.15, 0),
    "R38": (19.95, 35.5, 0), "RT38": (19.95, 37.15, 0),
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    "R32": (36.6, 22.6, 0), "RT32": (36.6, 24.25, 0), "R33": (36.6, 26.6, 0), "RT33": (36.6, 28.25, 0),
    "R34": (41.7, 26.9, 0), "RT34": (41.7, 28.55, 0),
    # (review pass 1: LINE_IN's column straight: C36 turned, its GND pad to the right, R35 turned, its LINE_IN pad down
    #  next to C36's: LINE_IN no longer detours over pins 15 .. 17, whose channel north UP / SCL / SDA need)
    # (C36 / R35: auto_place by the module's LINE_IN pin, 2026-11-15)
}
WIDTH = {"VDD3P3": 0.5, "VSYS": 0.5, "+3V3": 0.4, "VBUS": 0.4, "VUSB_D": 0.4, "SW": 0.4}
ORDER = ["UDP", "UDN", "USB_DP", "USB_DN", "XTAL_P", "XTAL_N", "XTAL_X1", "VDD_SPI", "CHIP_PU", "PWR_HOLD", "VBUS_SENSE", "VBANK_ADC", "BOOT",
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          ("VBAT_ADC", CY - 0.6, CX + 4.1, CY - 4.2, True)]
# (stage 2: pins 6 / 7 / 9 carry the charge pump, CLOCK and the cell's level: parts.py GPIO; YES / DOWN moved to the
#  chip's left side)
# (mini 2.2: GPIO1's lane carries the cell's level; stage 2: mini 2's VBUS_SENSE / PWR_HOLD lanes (pins 7 / 9) carry UP / DOWN)

board = pcbnew.BOARD()
nets = {}
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        ("R153", (50.3, 47.5)), ("R154", (19.4, 67.3)),   # (chain list 4)
        ("C102", (18.0, 57.0)), ("C103", (25.5, 57.0)),   # (the beat LEDs 3 / 4's 100 nF)
        # (the module, 2026-11-15: its 3V3 caps by pin 2, the EN RC by pin 3, the cell ADC's cap by pin 4 (the module's
        #  right side, turned 180), LINE_IN's R35 / C36 above pin 17)
        ("C17", (49.6, 69.5)), ("C16", (49.0, 71.0)), ("C7", (50.5, 59.3)), ("R8", (50.5, 60.6)),
        # (the digital LINE IN, 2026-11-15: each node's parts by its module pin, A (LINE_IN) over pin 17, B (LINE_SENSE)
        #  right of pin 12; the bias divider R33 / R34 stays by the jack, its C33 by the nodes)
        ("C32", (43.0, 50.9)), ("R32", (41.2, 50.9)), ("C30", (39.4, 50.9)), ("C31", (37.6, 50.9)), ("R30", (39.4, 49.6)),
        ("R31", (37.6, 49.6)), ("C33", (45.3, 50.9)),
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    RF_SEGS.append(("UDN", 0, a7[0], a7[1], a7[0], yb, 0.2))
    RF_SEGS.append(("UDN", 0, b7[0], b7[1], b7[0], yb, 0.2))
    RF_SEGS.append(("UDN", 0, a7[0], yb, b7[0], yb, 0.2))
    RF_SEGS.append(("UDN", 0, b7[0], yb, u4[0], u4[1], 0.2))   # (from B7's end of the bridge: clear of U5's VBUS pin)
    v2 = (b6[0] - 0.95, b6[1] + 1.05)              # (clear of SBU A8 left of B6, of both VBUS pads and of U5's pin 5)
    RF_SEGS.append(("UDP", 0, b6[0], b6[1], b6[0], yb, 0.2))
    RF_SEGS.append(("UDP", 0, b6[0], yb, v2[0], v2[1], 0.2))
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    RF_SEGS.append(("+3V3", 0, vb[0], vb[1], u5v[0], u5v[1], 0.25))   # (review pass 2: U5's REF on +3V3)
    FIXED_VIAS.append(("+3V3", vb[0], vb[1]))
    u1p, u3p = pad_center(pad_of(fps, "U5", "1")), pad_center(pad_of(fps, "U5", "3"))
    RF_SEGS.append(("UDP", 0, u6[0], u6[1], u1p[0], u1p[1], 0.2))     # (U5's flow-through: pin 6 -> 1, 4 -> 3, under it)
    RF_SEGS.append(("UDN", 0, u4[0], u4[1], u3p[0], u3p[1], 0.2))
    if FLOOR:                                    # (the fresh floorplan: the router takes the pair from U5 to R24 / R25)
        FIXED_VIAS.append(("UDP", v2[0], v2[1]))
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    for ref, pin in (("R24", "26"), ("R25", "25")):
        px, py = pad_center(pad_of(fps, "U1", pin))
        rx, ry = pad_center(pad_of(fps, ref, "2"))
        n = "USB_DP" if pin == "26" else "USB_DN"
        RF_SEGS.append((n, 0, px, py, px, ry + 0.75, 0.2))      # (stage 2: up, then a short slant into the pad)
        RF_SEGS.append((n, 0, px, ry + 0.75, rx, ry, 0.2))
    # VDD3P3's two pins (2 and 3) joined on top, at their pads' centre line
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    c28 = pad_center(pad_of(fps, "C28", "1"))
    RF_SEGS.append(("VDD3P3", 0, CX + 3.41, CY + 2.0, c28[0], c28[1], 0.2))
    FIXED_VIAS.append(("VDD3P3", CX + 4.2, CY + 2.0))
    # mini 2: LINE_IN (GPIO9, pin 14: the right side's top pin) straight up out of the corner, past pin 15, to C36 (100 nF
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
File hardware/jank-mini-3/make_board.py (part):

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        #  (review 2B R1) and blocked FB / EN / VIN's way out, 9 nets open in 2 of 2 attempts)
        "C100": (W - 8.0 + 3.6, H - 14.0 + 0.75, 0), "C101": (W - 8.0 + 3.6, H - 14.0 + 2.95, 0),   # (clear of L5's courtyard)
        # (the input cap up-left of VIN (pin 3): its track goes up and left, pins 2 (EN) / 1 (FB) escape upwards; on the
        #  right, over pins 1 / 2, it boxed EN in, 2 of 2 attempts left V5_EN / V5_FB open)
        "C104": (W - 8.0 - 2.2, H - 14.0 - 2.1, 180),
        # (U5, the USB ESD array, turned so its data pins 1 / 3 face the two USB-C above and its CC pins 4 / 6 face
        #  R160 / R161 below; at 0 the data lines wrapped round it and the router left UDP / CC1O open, round 3)
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

# tracks drawn before routing (locked: Freerouting keeps them): (net, (ref, pad), (ref, pad), width mm)
# (V5_SW: out to the left of U18's pin column, 1.15 mm off its SW pad, then in from the side: pin 4 (GND) above it)
DRAWN = [("V5_SW", ("L5", "2"), ("U18", "5"), 0.3, -1.15), ("VIN_B", ("L5", "1"), ("U18", "3"), 0.3, None)]
if MINI3:   # (U18 turned 90: L5 straight under the SW pin; VIN_B left to the router)
    DRAWN = [("V5_SW", ("L5", "2"), ("U18", "5"), 0.3, None)]


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def usb_pair(board, fps):
    """the data pair's run J1 -> U5 -> J4, drawn and locked: the geometry Freerouting found on the clean board of
    2026-11-19 (round 4), taken from the fan-out's ends. (Round 5: Freerouting routes GND first, and in 5 of 5 attempts
    its GND tracks from J1's ground pins walled J1's D+ / D- fan-out in, UDP / UDN left open.)
    D+: J1's join down to a via, under J1's lower D- via on the bottom, up again past it, along the top to J4's join,
    then down to a via, on the bottom to U5.1. D-: J1's lower D- via along the top to U5.3; J4's lower D- via to it."""
    pad = lambda r, n: next(p for p in fps[r].Pads() if p.GetNumber() == n).GetPosition()
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
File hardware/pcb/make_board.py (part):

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    for n, tp in ((9, "TP5"), (10, "TP6"), (11, "TP7"), (12, "TP8")):
        route(f"MOD_P{n - 5}", [u[n], at(TP[tp], 1)])
    # CLKR_IN / RSTR_IN down on the top to vias just past the TX lane (bottom, y 49.2) and OUT4's 10 ohm group's A pad,
    # then on the bottom: CLKR_IN straight to a via by U8's pin 2; RSTR_IN west of the 10 ohm group's standing part, east
    # along y 57.0 (between the front groups and the front switches' pins) to a via by U9's pin 2
    CV, RV = (64.8, 49.9), (62.9, 49.9)              # (CV east of the TX via's bottom stub at x 64.05)
    route("CLKR_IN", [u[7], (u[7][0], 46.4), (CV[0], 46.4), CV])
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    DBG.update(d5=d5, d4=d4, jt1=jt1, jr1=jr1, sw2=s, ta1=(ta1["A"], ta1["B"]), tb1=(tb1["A"], tb1["B"]))
    route("TIP1", [ta1["B"], (ta1["B"][0], 17.9), (d5[0], 17.9), d5])                       # (top, across)
    route("RING1", [tb1["B"], (tb1["B"][0], 17.9), (d4[0], 17.9), d4], SIG, BOT)            # (bottom, across)
    # the throws: RING1 pin 1 -> pin 6 straight under the body (top); TIP1 pin 3 -> pin 4 on the bottom through two vias
    # (its top diagonal would cut JT1's way out); TIP1's pin 4 via on to DIN 5, RING1 pin 6 down to DIN 4 (top)
    route("RING1", [s[1], s[6]])
    route("RING1", [s[6], d4])
    TV3, TV4 = (s[3][0] + 1.0, s[3][1] + 1.25), (s[4][0] - 1.0, s[4][1] + 1.15)
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    solid(C11, "2")
    # ======== the screen: a 0.96" 128 x 64 OLED module (HS96L03W2C03, 27.3 x 27.8) on a 2.54 mm header (J10) ========
    # The module floats 2.5 mm up on its header, its pin edge just in front of the XIAO, the glass towards the front; only
    # low parts under it (0805, SOT-23). Header pins GND VCC SCL SDA at y OY, x from OX: MIDI_TXB's bottom line (x 35.85)
    # passes between GND and VCC, MIDI_TX1's (y 22.6) ends above the row.
    J10X, J10Y = 34.58, 24.0                         # (pin 1; not OX / OY: those are the board's page offset)
    J10 = place(JANK, "OLED_0.96in_128x64_I2C_HS96L03W2C03", "J10", "OLED 0.96in 128x64", J10X, J10Y, 0)
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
